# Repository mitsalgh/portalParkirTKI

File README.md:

# portalParkirTKI

<!-- tes push -->

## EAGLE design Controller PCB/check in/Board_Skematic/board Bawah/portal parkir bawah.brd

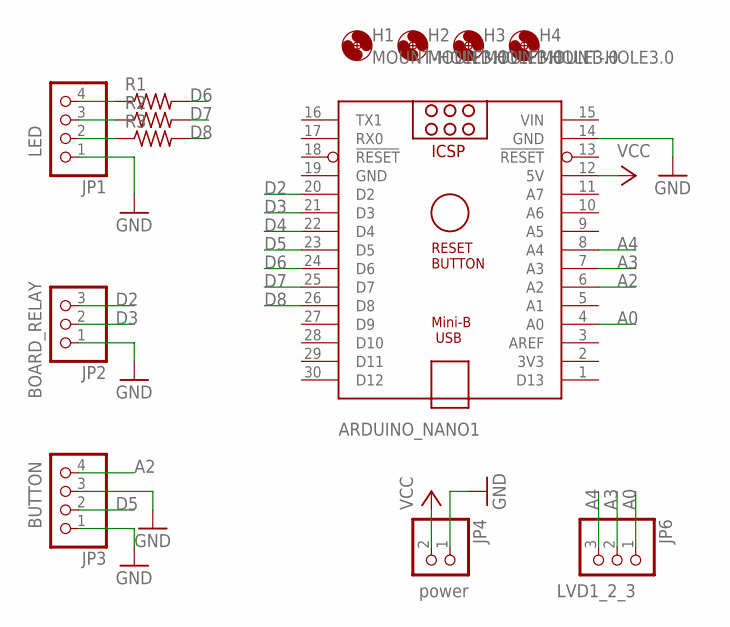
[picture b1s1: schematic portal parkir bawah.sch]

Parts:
ARDUINO_NANO1: ARDUINO_NANO
H1, H2, H3, H4: MOUNT-HOLE3.0; 3,0
JP1, JP3: PINHD-1X4; 1X04
JP2, JP6: PINHD-1X3; 1X03
JP4: PINHD-1X2; 1X02
R1, R2, R3: R-US_0309/12; 0309/12

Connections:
A0: ARDUINO_NANO1.4 (A0), JP6.1
A2: ARDUINO_NANO1.6 (A2), JP3.4
A3: ARDUINO_NANO1.7 (A3), JP6.2
A4: ARDUINO_NANO1.8 (A4), JP6.3
D2: ARDUINO_NANO1.20 (D2), JP2.3
D3: ARDUINO_NANO1.21 (D3), JP2.2
D4: ARDUINO_NANO1.22 (D4)
D5: ARDUINO_NANO1.23 (D5), JP3.2
D6: ARDUINO_NANO1.24 (D6), R1.2
D7: ARDUINO_NANO1.25 (D7), R2.2
D8: ARDUINO_NANO1.26 (D8), R3.2
GND: ARDUINO_NANO1.14 (GND), ARDUINO_NANO1.19 (GND), JP1.1, JP2.1, JP3.1, JP3.3, JP4.1
unnamed: JP1.2, R3.1
unnamed: JP1.3, R2.1
unnamed: JP1.4, R1.1
VCC: ARDUINO_NANO1.12 (5V), JP4.2
VIN: ARDUINO_NANO1.15 (VIN)

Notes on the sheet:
power
LVD1_2_3
BUTTON
BOARD_RELAY
LED

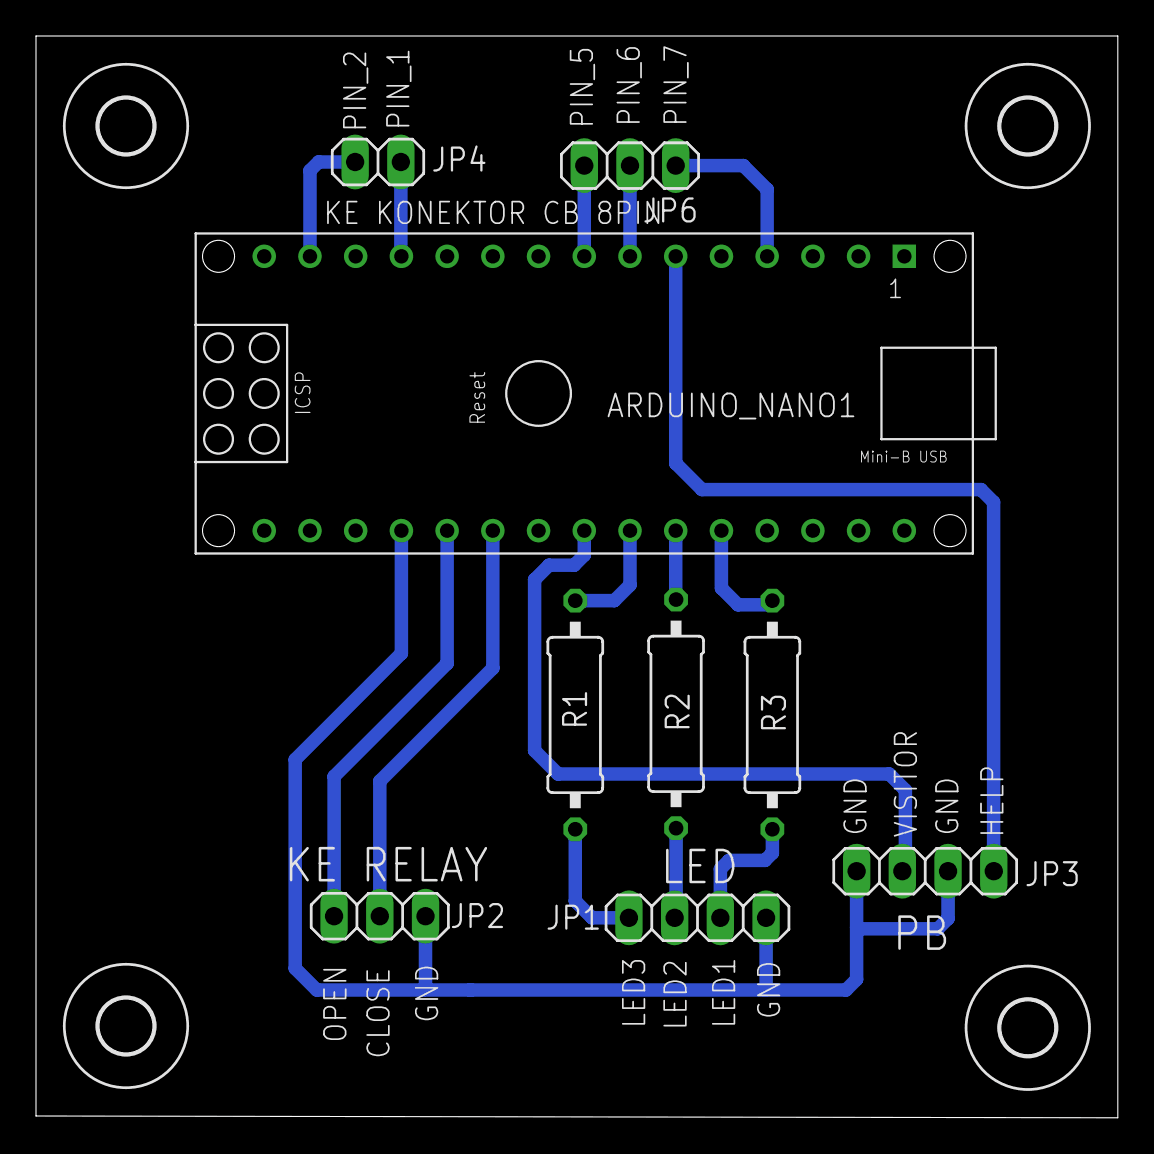
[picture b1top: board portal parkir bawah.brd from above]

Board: 2 copper layers, 60.1 x 60.1 mm, 13 parts (0 on the bottom side), 15 nets.

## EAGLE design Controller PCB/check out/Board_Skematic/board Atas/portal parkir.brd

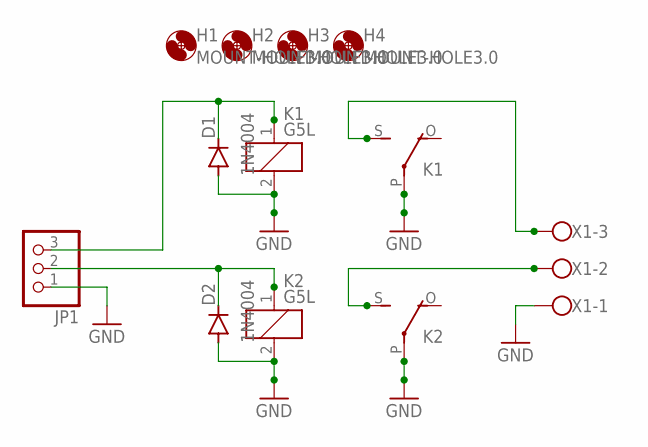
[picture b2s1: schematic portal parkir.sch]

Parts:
D1, D2: 1N4004; DO41-10
H1, H2, H3, H4: MOUNT-HOLE3.0; 3,0
JP1: PINHD-1X3; 1X03
K1, K2: G5L; G5LE
X1: W237-103

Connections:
GND: D1.A, D2.A, JP1.1, K1.2, K1.P, K2.2, K2.P, X1.1
unnamed: D1.C, JP1.3, K1.1
unnamed: D2.C, JP1.2, K2.1
unnamed: K2.S, X1.2
unnamed: K1.S, X1.3

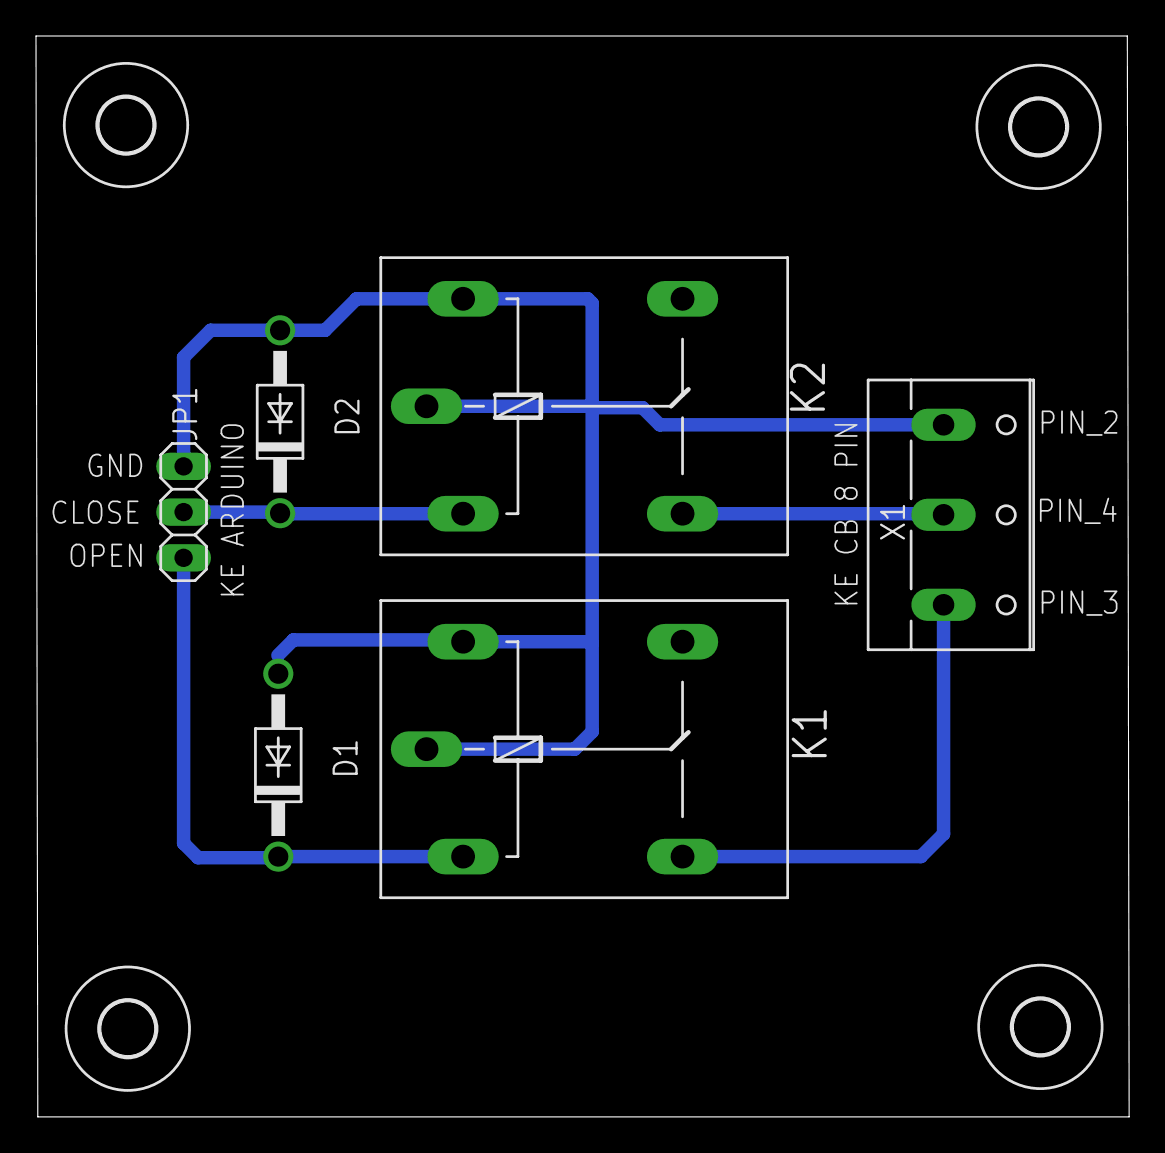
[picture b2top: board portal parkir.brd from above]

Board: 2 copper layers, 60.7 x 60.1 mm, 10 parts (0 on the bottom side), 5 nets.

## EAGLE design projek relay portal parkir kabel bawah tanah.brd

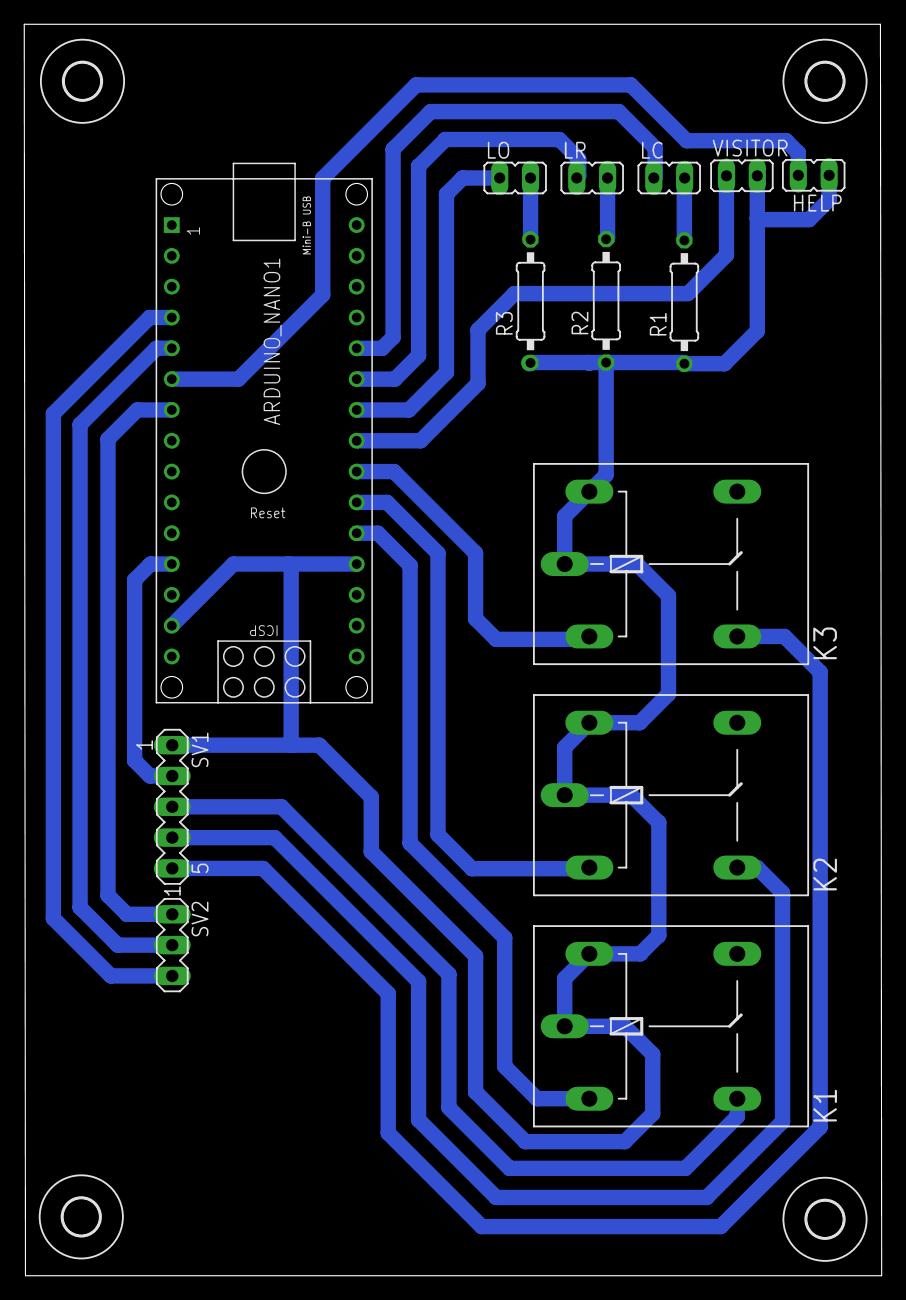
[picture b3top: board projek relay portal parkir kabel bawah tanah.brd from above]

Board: 2 copper layers, 70.7 x 103.1 mm, 18 parts (0 on the bottom side), 19 nets.

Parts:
ARDUINO_NANO1: ARDUINO_NANO
H1, H2, H3, H4: MOUNT-HOLE3.0; 3,0
HELP: JP1
K1, K2, K3: G5L; G5LE
LC: JP1
LO: JP1
LR: JP1
R1, R2, R3: 0207/10
SV1: MA05-1
SV2: MA03-1
VISITOR: JP1

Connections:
+5V: ARDUINO_NANO1.12, SV1.2
GND: ARDUINO_NANO1.14, ARDUINO_NANO1.19, HELP.1, K1.2, K1.P, K2.2, K2.P, K3.2, K3.P, R1.1, R2.1, R3.1, SV1.1, VISITOR.2
LC: ARDUINO_NANO1.26, LC.1
LO: ARDUINO_NANO1.24, LO.1
LR: ARDUINO_NANO1.25, LR.1
unnamed: ARDUINO_NANO1.6, HELP.2
unnamed: ARDUINO_NANO1.4, SV2.3
unnamed: ARDUINO_NANO1.5, SV2.2
unnamed: ARDUINO_NANO1.7, SV2.1
unnamed: K1.S, SV1.3
unnamed: K2.S, SV1.4
unnamed: ARDUINO_NANO1.23, VISITOR.1
unnamed: LO.2, R3.2
unnamed: LC.2, R1.2
unnamed: LR.2, R2.2
unnamed: K3.S, SV1.5
RC: ARDUINO_NANO1.21, K2.1
RO: ARDUINO_NANO1.20, K1.1
RS: ARDUINO_NANO1.22, K3.1

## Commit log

2023-09-01 test push
2023-09-01 tambah koma
2023-09-01 tambah koment
